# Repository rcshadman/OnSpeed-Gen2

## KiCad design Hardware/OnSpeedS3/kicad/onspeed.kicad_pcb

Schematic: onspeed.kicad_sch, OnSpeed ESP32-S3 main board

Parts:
C1: 22uF 100V; CP_Elec_8x10; Rating 100V, damps the input filter; above the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; MPN CS2A220M-CRF10; LCSC C116424
C2, C5: 100nF; C_0805_2012Metric; Rating 100V X7R; LCSC C28233
C3, C4: 2.2uF; C_1210_3225Metric; Rating 100V X7S; LCSC C86054
C6, C8, C47, C48: 2.2nF; C_0603_1608Metric; Rating 50V X7R; LCSC C1604
C7: 220pF; C_0805_2012Metric; Rating 50V C0G; LCSC C1805
C9, C10, C15, C20: 22uF; C_0805_2012Metric; Rating 25V X5R; LCSC C45783
C11, C12, C16, C18, C21, C22, C25, C26, C28, C29, C30, C31, C32, C33, C34, C36, C37, C40, C42, C43, C45, C49, C50, C51, C52, C53, C55, C57, C59: 100nF; C_0603_1608Metric; Rating 50V X7R; LCSC C14663
C13, C56: 4.7uF; C_0805_2012Metric; Rating 25V X5R; LCSC C1779
C14, C17, C19, C27, C41, C44, C46, C58: 10uF; C_0805_2012Metric; Rating 25V X5R; LCSC C15850
C23, C35: 1uF; C_0603_1608Metric; Rating 16V X7R; LCSC C15849
C24: 10nF; C_0603_1608Metric; Rating 50V X7R; LCSC C57112
C38, C39: 2.2uF; C_0603_1608Metric; Rating 16V X5R; LCSC C23630
C54: 4.7nF; C_0603_1608Metric; Rating 50V X7R; LCSC C53987
D1: SS210; D_SMA; MPN SS210; LCSC C14996
D2: SMBJ58A; D_SMB; MPN SMBJ58A; LCSC C10226
D3, D19: SS14; D_SMA; MPN SS14; LCSC C2480
D4: Green; LED_0603_1608Metric; MPN 19-217/GHC-YR1S2/3T; LCSC C72043
D5: Blue; LED_0603_1608Metric; MPN 19-217/BHC-ZL1M2RY/3T; LCSC C72041
D6, D7, D8, D10, D11, D12, D13, D14: 15V bidir ESD; D_SOD-323; MPN PESD15VL1BA; LCSC C2985482
D9: 24V bidir ESD; D_SOD-323; MPN PESD24VL1BA; LCSC C314263
D15, D16, D17, D18: BAT54S; SOT-23; MPN BAT54SLT1G; LCSC C19726
D20: PESD2CAN; SOT-23; MPN PESD2CAN; LCSC C2687131
F1: 0.75A 60V PTC; Fuse_2920_7451Metric; MPN MF-SM075/60-2; LCSC C210842
F2: 0.1A 15V PTC; Fuse_0603_1608Metric; MPN BSMD0603-010-15V; LCSC C883088
FB1: 220R@100MHz 2A; L_0805_2012Metric; MPN BLM21PG221SN1D; LCSC C85840
FB2, FB3, FB4: 600R@100MHz 1.3A; L_0603_1608Metric; MPN BLM18KG601SN1D; LCSC C85833
FID1, FID2, FID3: Fiducial; Fiducial_1mm_Mask2mm
H1, H2, H3, H4: M3; MountingHole_3.2mm_M3_Pad_Via
J1: USB-C 16P; USB_C_Receptacle_HRO_TYPE-C-31-M-12; MPN TYPE-C-31-M-12; LCSC C165948
J2: DA-15 female; DSUB-15_Female_Horizontal_P2.77x2.84mm_EdgePinOffset9.40mm_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; MPN DS1037-15FNAKT74-0CC; LCSC C77835
J3: JST-GH 4P; JST_GH_SM04B-GHS-TB_1x04-1MP_P1.25mm_Horizontal; MPN SM04B-GHS-TB(LF)(SN); LCSC C189895
J4: DE-9 male; DSUB-9_Male_Horizontal_P2.77x2.84mm_EdgePinOffset9.40mm_Hol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; MPN DS1037-09MNAKT74-0CC; LCSC C75750
J5: microSD push-pull; microSD_HC_Molex_104031-0811; MPN 104031-0811; LCSC C585350
JP1: CAN term; SolderJumper-2_P1.3mm_Open_RoundedPad1.0x1.5mm
L1: 33uH 1.8A shielded; L_Changjiang_FNR6045S; MPN FNR6045S330MT; LCSC C168083
R1: 330k; R_0603_1608Metric; LCSC C23137
R2, R4, R6, R9: 100k; R_0603_1608Metric; LCSC C25803
R3, R5: 31.6k; R_0603_1608Metric; LCSC C25967
R7: 150k; R_0603_1608Metric; LCSC C22807
R8: 8.2k; R_0603_1608Metric; LCSC C25981
R10, R11: 5.1k; R_0603_1608Metric; LCSC C23186
R12, R15, R38, R40, R42, R44: 470; R_0603_1608Metric; LCSC C23179
R13, R14, R37, R50, R52, R53, R54, R55, R56, R57: 10k; R_0603_1608Metric; LCSC C25804
R16, R25: 1k; R_0603_1608Metric; LCSC C21190
R17: 20k; R_0603_1608Metric; LCSC C4184
R18, R24: 150; R_0603_1608Metric; LCSC C22808
R19, R21, R22: 22k; R_0603_1608Metric; LCSC C31850
R20, R23: 5.6k; R_0603_1608Metric; LCSC C23189
R26: 0; R_0603_1608Metric; LCSC C21189
R27, R32: 200k; R_0603_1608Metric; LCSC C25811
R28, R29, R30, R31, R33, R34, R35, R36: 4.7k; R_0603_1608Metric; LCSC C23162
R39, R43: 560; R_0603_1608Metric; LCSC C23204
R41, R45: 100; R_0603_1608Metric; LCSC C22775
R46, R47, R48, R49: 120; R_0603_1608Metric; LCSC C22787
R51: 33; R_0603_1608Metric; LCSC C23140
SW1, SW2: Tactile 4.2x3.2mm; SW_SPST_PTS810; MPN PTS810SJG250SMTRLFS; LCSC C221895
TP1: VIN; TestPoint_Pad_D1.5mm
TP2: +5V; TestPoint_Pad_D1.5mm
TP3: +3V3; TestPoint_Pad_D1.5mm
TP4, TP5: GND; TestPoint_Pad_D1.5mm
TP6: EN; TestPoint_Pad_D1.5mm
TP7: BOOT; TestPoint_Pad_D1.5mm
TP8: U0TXD; TestPoint_Pad_D1.5mm
TP9: U0RXD; TestPoint_Pad_D1.5mm
U1: LM5164DDAR; SOIC-8-1EP_3.9x4.9mm_P1.27mm_EP2.95x4.9mm_Mask2.71x3.4mm_Th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; MPN LM5164DDAR; LCSC C477928
U2: USBLC6-2SC6; SOT-23-6; MPN USBLC6-2SC6; LCSC C7519
U3: LDL1117S33R; SOT-223-3_TabPin2; MPN LDL1117S33R; LCSC C435835
U4: ESP32-S3-WROOM-1-N8; ESP32-S3-WROOM-1_BodyCourtyard; MPN ESP32-S3-WROOM-1-N8; LCSC C2913198
U5, U6: MS4525DO-DS5AI001DP; MS4525DO_DIP8_500mil; MPN MS4525DO-DS5AI001DP
U7: SSCSRNN1.6BA7A3; Honeywell_SSC_SIP4_RN; MPN SSCSRNN1.6BA7A3
U8, U9: PCA9306DCUR; VSSOP-8_2.3x2mm_P0.5mm; MPN PCA9306DCUR; LCSC C33196
U10: ISM330DHCX; LGA-14_3x2.5mm_P0.5mm_LayoutBorder3x4y; MPN ISM330DHCXTR; LCSC C2655101
U11: PCM5102APWR; TSSOP-20_4.4x6.5mm_P0.65mm; MPN PCM5102APWR; LCSC C107671
U12: SP3232EEN-L/TR; SOIC-16_3.9x9.9mm_P1.27mm; MPN SP3232EEN-L/TR; LCSC C9378
U13: TJA1051T/3/1J; SOIC-8_3.9x4.9mm_P1.27mm; MPN TJA1051T/3/1J; LCSC C38695

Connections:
3V3_OUT_F: D19.2 (A), F2.2
+3V3: C15.1, C16.1, C20.1, C21.1, C22.1, C45.1, C46.1, C53.1, C57.1, C58.1, C59.1, D15.2 (K), D16.2 (K), D17.2 (K), D18.2 (K), F2.1, FB2.1, FB3.1, J5.4 (VDD), R9.2, R12.1, R13.1, R14.1, R17.1, R22.1, R52.1, R53.1, R54.1, R55.1, R56.1, R57.1, TP3.1, U3.2 (VO), U4.2 (3V3), U11.20 (DVDD), U12.16 (VCC), U13.5 (VIO)
+3V3_A: C19.1, C41.1, C42.1, C43.1, C44.1, FB3.2, U11.1 (CPVDD), U11.8 (AVDD)
+3V3_S: C17.1, C18.1, C30.1, C31.1, C32.1, C33.1, C34.1, C35.1, FB2.2, J3.1, R28.1, R29.1, R33.1, R34.1, U7.2 (VSUPPLY), U8.2 (VREF1), U9.2 (VREF1), U10.5 (VDDIO), U10.8 (VDD), U10.12 (CS)
+5V: C6.2, C9.1, C10.1, C11.1, C14.1, C55.1, C56.1, D3.1 (K), FB4.1, L1.2, R4.1, TP2.1, U3.3 (VI), U13.3 (VCC)
+5V_S: C27.1, C28.1, C29.1, FB4.2, R27.1, R30.1, R31.1, R32.1, R35.1, R36.1, U5.2 (VDD), U6.2 (VDD)
AUDIO_GND: J2.15, R26.1
AUDL_F: C47.1, R38.2, R39.1
AUDL_P: R39.2, R40.1, R41.1
AUDR_F: C48.1, R42.2, R43.1
AUDR_P: R43.2, R44.1, R45.1
BOOM_RX: D18.3 (COM), R25.2, U4.7 (IO7)
BOOT: R14.2, SW2.1, TP7.1, U4.27 (IO0)
BUCK_BST: C8.1, U1.7 (BST)
BUCK_EN: R1.2, R2.1, U1.3 (EN/UVLO)
BUCK_FB: C7.2, R4.2, R5.1, U1.5 (FB)
BUCK_RA: C6.1, C7.1, R6.2
BUCK_RON: R3.1, U1.4 (RON)
BUCK_SW: C8.2, L1.1, R6.1, U1.8 (SW)
CANH: D20.1 (K), J4.7, JP1.1 (A), U13.7 (CANH)
CANL: D20.2 (K), J4.2, R48.2, R49.2, U13.6 (CANL)
CAN_MID: C54.1, R46.2, R47.2, R48.1, R49.1
CAN_RX: U4.4 (IO4), U13.4 (RXD)
CAN_S: R50.1, U4.30 (IO37), U13.8 (S)
CAN_TH: JP1.2 (B), R46.1, R47.1
CAN_TX: U4.24 (IO47), U13.1 (TXD)
DAC_CAPM: C38.2, U11.4 (CAPM)
DAC_CAPP: C38.1, U11.2 (CAPP)
DAC_L: R38.1, U11.6 (OUTL)
DAC_LDOO: C40.1, U11.18 (LDOO)
DAC_R: R42.1, U11.7 (OUTR)
DAC_VNEG: C39.1, U11.5 (VNEG)
DAC_XSMT: R37.1, U4.23 (IO21), U11.17 (XSMT)
DISP_TX: R24.1, U4.18 (IO10)
EFIS_RX: U4.8 (IO15), U12.12 (R1OUT)
EFIS_TX: U4.19 (IO11), U12.11 (T1IN)
EN: C23.1, R13.2, SW1.1, TP6.1, U4.3 (EN)
FLAP_ADC: C25.1, D16.3 (COM), R19.2, R20.1, U4.39 (IO1)
GND: C1.2, C2.2, C3.2, C4.2, C5.2, C9.2, C10.2, C11.2, C12.2, C13.2, C14.2, C15.2, C16.2, C17.2, C18.2, C19.2, C20.2, C21.2, C22.2, C23.2, C24.2, C25.2, C26.2, C27.2, C28.2, C29.2, C30.2, C31.2, C32.2, C33.2, C34.2, C35.2, C36.2, C37.2, C39.2, C40.2, C41.2, C42.2, C43.2, C44.2, C45.2, C46.2, C47.2, C48.2, C51.2, C52.2, C53.2, C54.2, C55.2, C56.2, C57.2, C58.2, C59.2, D2.2 (A), D4.1 (K), D5.1 (K), D6.2 (A2), D7.2 (A2), D8.2 (A2), D9.2 (A2), D10.2 (A2), D11.2 (A2), D12.2 (A2), D13.2 (A2), D14.2 (A2), D15.1 (A), D16.1 (A), D17.1 (A), D18.1 (A), D20.3 (A), H1.1, H2.1, H3.1, H4.1, J1.A1 (GND), J1.A12 (GND), J1.B1 (GND), J1.B12 (GND), J1.S1 (SHIELD), J2.0 (PAD), J2.14, J3.4, J4.0 (PAD), J4.3, J4.5, J4.8, J5.6 (VSS), J5.10 (DET_A), J5.11 (SHIELD), R2.2, R3.2, R5.2, R8.2, R10.2, R11.2, R20.2, R23.2, R26.2, R37.2, R40.2, R44.2, R50.2, SW1.2, SW2.2, TP4.1, TP5.1, U1.1 (GND), U1.9 (EP), U2.2 (GND), U3.1 (GND), U4.1 (GND), U4.40 (GND), U4.41 (GND), U5.1 (GND), U6.1 (GND), U7.1 (GND), U8.1 (GND), U9.1 (GND), U10.1 (SDO/SA0), U10.2 (SDX), U10.3 (SCX), U10.6 (GND), U10.7 (GND), U11.3 (CPGND), U11.9 (AGND), U11.10 (DEMP), U11.11 (FLT), U11.12 (SCK), U11.16 (FMT), U11.19 (DGND), U12.10 (T2IN), U12.15 (GND), U13.2 (GND)
GPS_RX: U4.9 (IO16), U12.9 (R2OUT)
I2CA5_SCL: R31.2, U5.4 (SCL), U8.6 (SCL2)
I2CA5_SDA: R30.2, U5.3 (SDA), U8.5 (SDA2)
I2CA_SCL: R29.2, U4.17 (IO9), U7.4 (SCL), U8.3 (SCL1)
I2CA_SDA: R28.2, U4.12 (IO8), U7.3 (SDA), U8.4 (SDA1)
I2CA_VREF2: C36.1, R27.2, U8.7 (VREF2), U8.8 (EN)
I2CB5_SCL: R36.2, U6.4 (SCL), U9.6 (SCL2)
I2CB5_SDA: R35.2, U6.3 (SDA), U9.5 (SDA2)
I2CB_SCL: J3.2, R34.2, U4.11 (IO18), U9.3 (SCL1), U10.13 (SCL)
I2CB_SDA: J3.3, R33.2, U4.10 (IO17), U9.4 (SDA1), U10.14 (SDA)
I2CB_VREF2: C37.1, R32.2, U9.7 (VREF2), U9.8 (EN)
I2S_BCK: U4.20 (IO12), U11.13 (BCK)
I2S_DIN: U4.22 (IO14), U11.14 (DIN)
I2S_LRCK: U4.21 (IO13), U11.15 (LRCK)
IMU_INT1: U4.28 (IO35), U10.4 (INT1)
LED_OUT: R18.1, U4.6 (IO6)
LED_PWR: D4.2 (A), R12.2
LED_STAT: D5.2 (A), R15.2
PGOOD: R9.1, U1.6 (PGOOD), U4.25 (IO48)
RS232_EFIS_IN: J2.2, U12.13 (R1IN)
RS232_EFIS_OUT: J2.12, U12.14 (T1OUT)
RS232_GPS_IN: J2.4, U12.8 (R2IN)
RS_C1N: C49.2, U12.3 (C1-)
RS_C1P: C49.1, U12.1 (C1+)
RS_C2N: C50.2, U12.5 (C2-)
RS_C2P: C50.1, U12.4 (C2+)
RS_VN: C52.1, U12.6 (VS-)
RS_VP: C51.1, U12.2 (VS+)
SD_CLK: R51.1, U4.32 (IO39)
SD_CLK_C: J5.5 (CLK), R51.2
SD_CMD: J5.3 (CMD), R52.2, U4.33 (IO40)
SD_D0: J5.7 (DAT0), R53.2, U4.34 (IO41)
SD_D1: J5.8 (DAT1), R54.2
SD_D2: J5.1 (DAT2), R55.2
SD_D3: J5.2 (DAT3/CD), R56.2, U4.35 (IO42)
SD_DET: J5.9 (DET_B), R57.2, U4.29 (IO36)
STAT_LED: R15.1, U4.31 (IO38)
SW_IN: C24.1, D15.3 (COM), R16.2, R17.2, U4.5 (IO5)
U0RXD: TP9.1, U4.36 (RXD0)
U0TXD: TP8.1, U4.37 (TXD0)
USB_CC1: J1.A5 (CC1), R10.1
USB_CC2: J1.B5 (CC2), R11.1
USB_DM: J1.A7 (D-), J1.B7 (D-), U2.1 (I/O1), U2.6 (I/O1), U4.13 (IO19)
USB_DP: J1.A6 (D+), J1.B6 (D+), U2.3 (I/O2), U2.4 (I/O2), U4.14 (IO20)
VBUS: C13.1, D3.2 (A), J1.A4 (VBUS), J1.A9 (VBUS), J1.B4 (VBUS), J1.B9 (VBUS), U2.5 (VBUS)
VIN: C1.1, C3.1, C4.1, C5.1, FB1.2, R1.1, R7.1, TP1.1, U1.2 (VIN)
VIN_F: D1.2 (A), F1.2
VIN_P: C2.1, D1.1 (K), D2.1 (K), FB1.1
VIN_RAW: F1.1, J2.1
VIN_SENSE: C12.1, R7.2, R8.1, U4.15 (IO3)
VOL_ADC: C26.1, D17.3 (COM), R21.2, R22.2, R23.1, U4.38 (IO2)
X_3V3: D13.1 (A1), D19.1 (K), J2.11 (P111)
X_AUD_L: D8.1 (A1), J2.6, R41.2
X_AUD_R: D10.1 (A1), J2.8, R45.2
X_BOOM: D14.1 (A1), J2.13, R25.1
X_DISP: D11.1 (A1), J2.9, R24.2
X_FLAP: D9.1 (A1), J2.7, R19.1
X_LED: D7.1 (A1), J2.5, R18.2
X_SW: D6.1 (A1), J2.3, R16.1
X_VOL: D12.1 (A1), J2.10, R21.1

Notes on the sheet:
1 Aircraft power in, protection, 5 V buck (LM5164)
2 USB-C (power + flashing), 3.3 V LDO, filtered rails
3 ESP32-S3-WROOM-1-N8
4 DB-15 harness (Gen2 pinout) and line protection
5 Pressure sensors (Gen2 positions) and ISM330DHCX IMU
6 Audio: PCM5102A and 600 ohm intercom pad
7 RS-232 (EFIS in/out, GPS in): SP3232E
8 CAN-FiX (MakerPlane): TJA1051T/3, DE-9 male
9 microSD logging (1-bit SDMMC)
10 Mechanical: grounded M3 holes, fiducials
Order of protection: PTC (over-current) -> SS210 (reverse polarity) -> SMBJ58A (clamps 93.6 V, under the LM5164 100 V rating, so load dump and 28 V surges ride through) -> ferrite + 47 uF damped filter -> LM5164 (100 V rated).
USB VBUS feeds +5V through SS14, so the board runs and flashes from a laptop with no aircraft power. With both present the buck (5.0 V) carries the load.
Strapping: IO0 BOOT button + 10k up; IO3 carries the VIN monitor (strap only used if the JTAG eFuse is set); IO45/IO46 left open (internal pull-downs: 3.3 V flash, normal boot).
Every external line has a 15 V bidirectional ESD diode at the connector (flap may see 14 V; audio swings both ways). RS-232 lines rely on the SP3232E's own +/-15 kV protection.
Two MS4525DO share address 0x28, so each sits on its own bus (as the firmware expects).
Pad: 2.1 Vrms DAC -> about 0.39 Vrms into a 600 ohm panel input, source impedance about 420 ohm. DAC load stays above 1 kohm. PCM5102A outputs are ground-centred, so no DC blocking is needed.
Unused T2IN tied low so it cannot float.
DE-9: 2 CAN-L, 7 CAN-H, 3 CAN GND, 5 GND, 8 shield; pin 1 bus power not used.

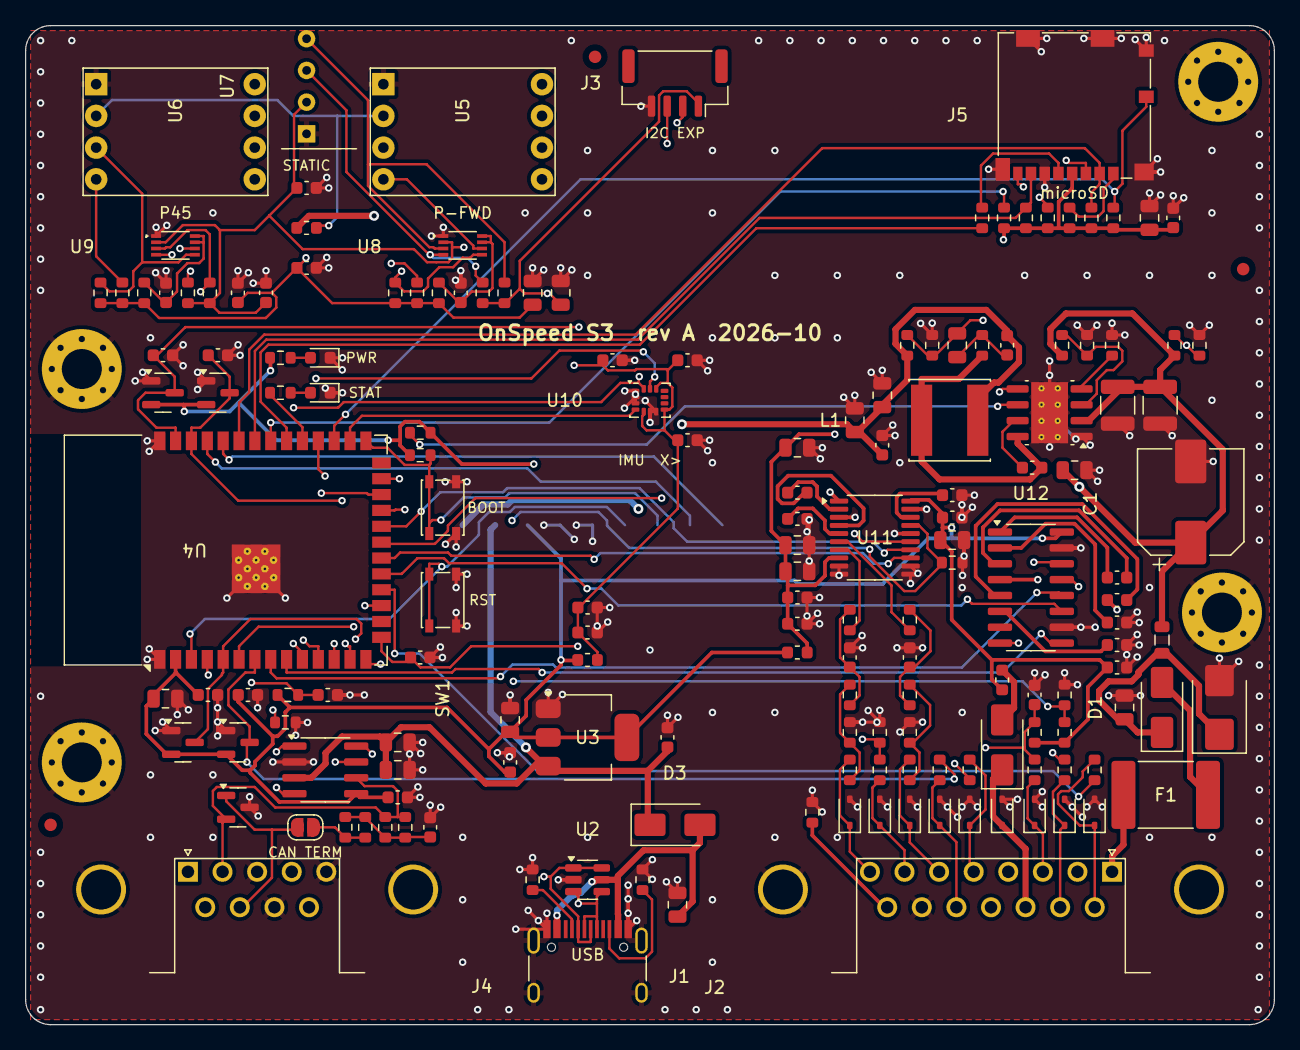
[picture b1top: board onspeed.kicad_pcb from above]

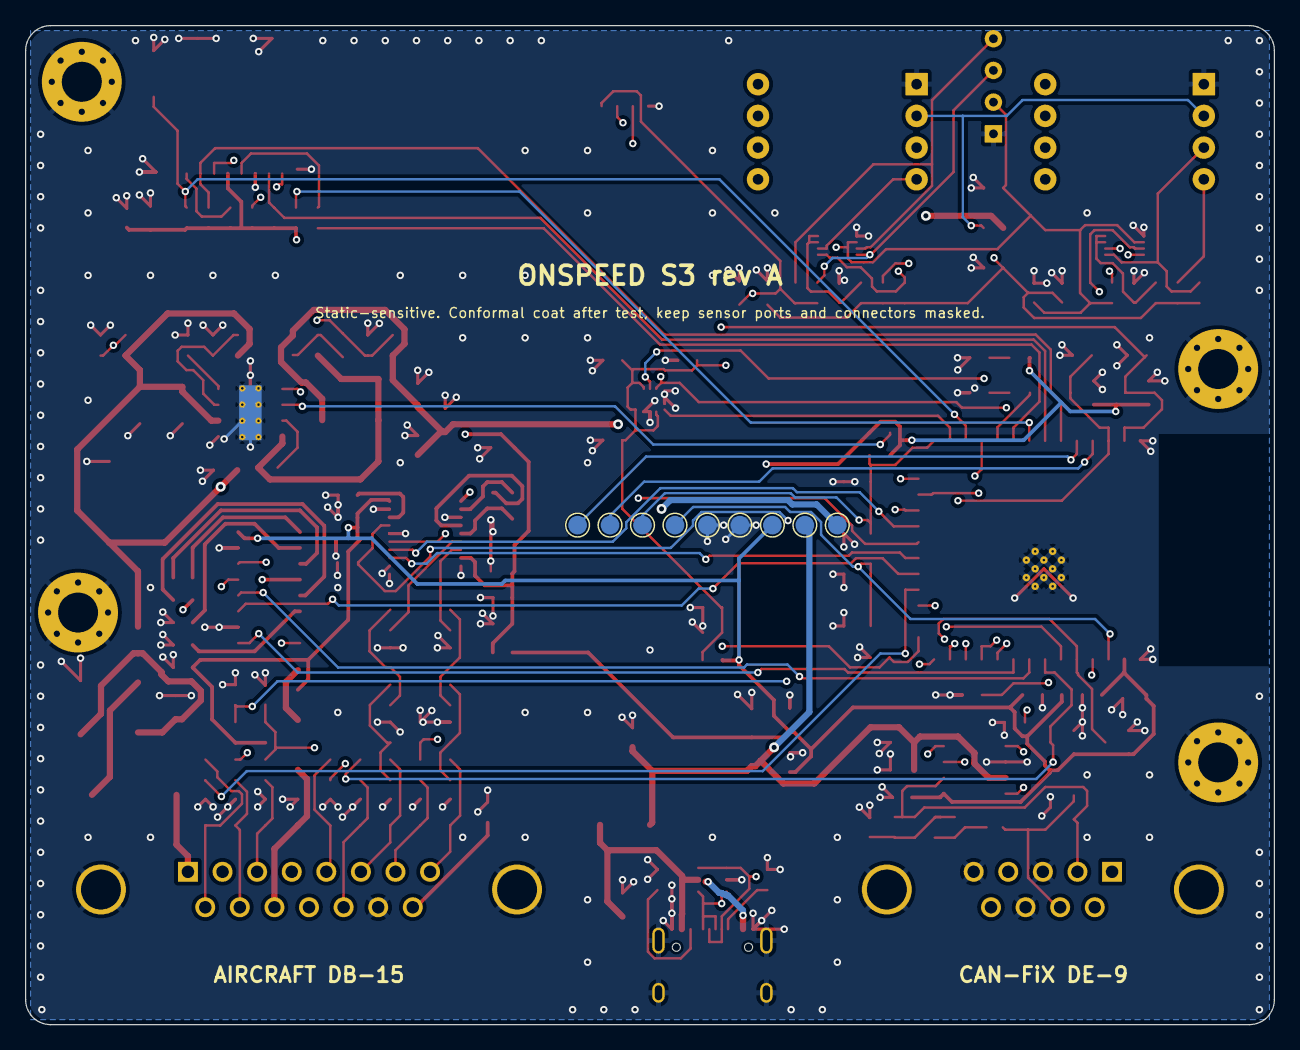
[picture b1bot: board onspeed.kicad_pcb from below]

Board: 4 copper layers, 100.0 x 80.0 mm, 180 parts (9 on the bottom side), 99 nets.

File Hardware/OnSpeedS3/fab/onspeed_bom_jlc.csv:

Comment,Designator,Footprint,LCSC Part #,MPN,Qty
22uF 100V,C1,CP_Elec_8x10,C116424,CS2A220M-CRF10,1
100nF,"C2,C5",C_0805_2012Metric,C28233,,2
2.2uF,"C3,C4",C_1210_3225Metric,C86054,,2
2.2nF,"C6,C8,C47,C48",C_0603_1608Metric,C1604,,4
220pF,C7,C_0805_2012Metric,C1805,,1
22uF,"C9,C10,C15,C20",C_0805_2012Metric,C45783,,4
100nF,"C11,C12,C16,C18,C21,C22,C25,C26,C28,C29,C30,C31,C32,C33,C34,C36,C37,C40,C42,C43,C45,C49,C50,C51,C52,C53,C55,C57,C59",C_0603_1608Metric,C14663,,29
4.7uF,"C13,C56",C_0805_2012Metric,C1779,,2
10uF,"C14,C17,C19,C27,C41,C44,C46,C58",C_0805_2012Metric,C15850,,8
1uF,"C23,C35",C_0603_1608Metric,C15849,,2
10nF,C24,C_0603_1608Metric,C57112,,1
2.2uF,"C38,C39",C_0603_1608Metric,C23630,,2
4.7nF,C54,C_0603_1608Metric,C53987,,1
SS210,D1,D_SMA,C14996,SS210,1
SMBJ58A,D2,D_SMB,C10226,SMBJ58A,1
SS14,"D3,D19",D_SMA,C2480,SS14,2
Green,D4,LED_0603_1608Metric,C72043,19-217/GHC-YR1S2/3T,1
Blue,D5,LED_0603_1608Metric,C72041,19-217/BHC-ZL1M2RY/3T,1
15V bidir ESD,"D6,D7,D8,D10,D11,D12,D13,D14",D_SOD-323,C2985482,PESD15VL1BA,8
24V bidir ESD,D9,D_SOD-323,C314263,PESD24VL1BA,1
BAT54S,"D15,D16,D17,D18",SOT-23,C19726,BAT54SLT1G,4
PESD2CAN,D20,SOT-23,C2687131,PESD2CAN,1
0.75A 60V PTC,F1,Fuse_2920_7451Metric,C210842,MF-SM075/60-2,1
0.1A 15V PTC,F2,Fuse_0603_1608Metric,C883088,BSMD0603-010-15V,1
220R@100MHz 2A,FB1,L_0805_2012Metric,C85840,BLM21PG221SN1D,1
600R@100MHz 1.3A,"FB2,FB3,FB4",L_0603_1608Metric,C85833,BLM18KG601SN1D,3
USB-C 16P,J1,USB_C_Receptacle_HRO_TYPE-C-31-M-12,C165948,TYPE-C-31-M-12,1
DA-15 female,J2,DSUB-15_Female_Horizontal_P2.77x2.84mm_EdgePinOffset9.40mm_Holes33.32mm,C77835,DS1037-15FNAKT74-0CC,1
JST-GH 4P,J3,JST_GH_SM04B-GHS-TB_1x04-1MP_P1.25mm_Horizontal,C189895,SM04B-GHS-TB(LF)(SN),1
DE-9 male,J4,DSUB-9_Male_Horizontal_P2.77x2.84mm_EdgePinOffset9.40mm_Holes24.99mm,C75750,DS1037-09MNAKT74-0CC,1
microSD push-pull,J5,microSD_HC_Molex_104031-0811,C585350,104031-0811,1
33uH 1.8A shielded,L1,L_Changjiang_FNR6045S,C168083,FNR6045S330MT,1
330k,R1,R_0603_1608Metric,C23137,,1
100k,"R2,R4,R6,R9",R_0603_1608Metric,C25803,,4
31.6k,"R3,R5",R_0603_1608Metric,C25967,,2
150k,R7,R_0603_1608Metric,C22807,,1
8.2k,R8,R_0603_1608Metric,C25981,,1
5.1k,"R10,R11",R_0603_1608Metric,C23186,,2
470,"R12,R15,R38,R40,R42,R44",R_0603_1608Metric,C23179,,6
10k,"R13,R14,R37,R50,R52,R53,R54,R55,R56,R57",R_0603_1608Metric,C25804,,10
1k,"R16,R25",R_0603_1608Metric,C21190,,2
20k,R17,R_0603_1608Metric,C4184,,1
150,"R18,R24",R_0603_1608Metric,C22808,,2
22k,"R19,R21,R22",R_0603_1608Metric,C31850,,3
5.6k,"R20,R23",R_0603_1608Metric,C23189,,2
0,R26,R_0603_1608Metric,C21189,,1
200k,"R27,R32",R_0603_1608Metric,C25811,,2
4.7k,"R28,R29,R30,R31,R33,R34,R35,R36",R_0603_1608Metric,C23162,,8
560,"R39,R43",R_0603_1608Metric,C23204,,2
100,"R41,R45",R_0603_1608Metric,C22775,,2
120,"R46,R47,R48,R49",R_0603_1608Metric,C22787,,4
33,R51,R_0603_1608Metric,C23140,,1
Tactile 4.2x3.2mm,"SW1,SW2",SW_SPST_PTS810,C221895,PTS810SJG250SMTRLFS,2
LM5164DDAR,U1,SOIC-8-1EP_3.9x4.9mm_P1.27mm_EP2.95x4.9mm_Mask2.71x3.4mm_ThermalVias,C477928,LM5164DDAR,1
USBLC6-2SC6,U2,SOT-23-6,C7519,USBLC6-2SC6,1
LDL1117S33R,U3,SOT-223-3_TabPin2,C435835,LDL1117S33R,1
ESP32-S3-WROOM-1-N8,U4,ESP32-S3-WROOM-1_BodyCourtyard,C2913198,ESP32-S3-WROOM-1-N8,1
MS4525DO-DS5AI001DP,"U5,U6",MS4525DO_DIP8_500mil,,MS4525DO-DS5AI001DP,2
SSCSRNN1.6BA7A3,U7,Honeywell_SSC_SIP4_RN,,SSCSRNN1.6BA7A3,1
PCA9306DCUR,"U8,U9",VSSOP-8_2.3x2mm_P0.5mm,C33196,PCA9306DCUR,2
ISM330DHCX,U10,LGA-14_3x2.5mm_P0.5mm_LayoutBorder3x4y,C2655101,ISM330DHCXTR,1
PCM5102APWR,U11,TSSOP-20_4.4x6.5mm_P0.65mm,C107671,PCM5102APWR,1
SP3232EEN-L/TR,U12,SOIC-16_3.9x9.9mm_P1.27mm,C9378,SP3232EEN-L/TR,1
TJA1051T/3/1J,U13,SOIC-8_3.9x4.9mm_P1.27mm,C38695,TJA1051T/3/1J,1

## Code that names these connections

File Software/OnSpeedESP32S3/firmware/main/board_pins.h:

// Pin map for the ESP32-S3-DevKitC-1 (ESP32-S3-WROOM-1 N8R8) prototype and the OnSpeed S3 custom board
// (Hardware/OnSpeedS3, WROOM-1 N8, no PSRAM). Every pin below is the same on both. Avoided: strapping pins 0/45/46 and USB 19/20
// (console runs on USB-Serial-JTAG), 43/44 (UART0, boot ROM output). GPIO3 is a strap only once the JTAG-select eFuse is burned, so the
// custom board uses it for the VIN monitor. On the DevKitC, 35-37 are octal PSRAM and 38/48 the RGB LED; the custom board (N8, no PSRAM)
// uses them in the ONSPEED_BOARD_S3 block below.
// Source: /mnt/project-files/onspeed-port/hardware-verification.md (pin audit).
#pragma once

// I2C bus A: Pfwd MS4525DO (0x28) + static SSCSRNN1.6BA7A3 (0x78). External 4.7k pull-ups required.
#define PIN_I2C_A_SDA 8
#define PIN_I2C_A_SCL 9
// I2C bus B: P45 MS4525DO (0x28) + ISM330DHCX IMU (0x6A). External 4.7k pull-ups required.
#define PIN_I2C_B_SDA 17
#define PIN_I2C_B_SCL 18
#define I2C_HZ 400000          // ESP32-S3 maximum (Gen2 Teensy ran these buses faster)

// Analog inputs on ADC1 (ADC2 is unusable while Wi-Fi runs)
#define ADC_CH_FLAP 0          // GPIO1, DB-15 pin 7, Gen2 divider 22k/5.6k + 100 nF
#define ADC_CH_VOLUME 1        // GPIO2, DB-15 pin 10

// PCM5102A I2S DAC
#define PIN_I2S_BCLK 12
#define PIN_I2S_WS 13
#define PIN_I2S_DOUT 14
#define PIN_DAC_XSMT 21        // 10k pull-down on the board keeps the DAC muted until firmware is up

// Serial
#define PIN_DISPLAY_TX 10      // M5Stack "#1" sentences, 115200 8N1, 3.3 V TTL
#define PIN_EFIS_TX 11         // MAX3232 T1IN
#define PIN_EFIS_RX 15         // MAX3232 R1OUT (Garmin G5 / G3X / Dynon / MGL)
#define PIN_GPS_RX 16          // MAX3232 R2OUT (VN-300)
#define PIN_BOOM_RX 7          // 3.3 V TTL only

// CAN-FiX (MakerPlane EFIS), 125 kbit/s. Custom board: TJA1051T/3 (VCC 5 V, VIO 3.3 V)
#define PIN_CAN_TX 47
#define PIN_CAN_RX 4

// Panel
#define PIN_PANEL_SWITCH 5
#define PIN_AOA_LED 6

// microSD, 1-bit SDMMC
#define PIN_SD_CLK 39
#define PIN_SD_CMD 40
#define PIN_SD_D0 41
#define PIN_SD_D3 42

// Custom board only (OnSpeed S3 rev A). Define ONSPEED_BOARD_S3 when building for it. On the DevKitC these
// GPIOs carry the octal PSRAM (35-37) and the RGB LED (38, 48), so they must stay unused there.
#ifdef ONSPEED_BOARD_S3
#define PIN_IMU_INT1 35        // ISM330DHCX INT1, push-pull, no pull-up
#define PIN_SD_DET 36          // card detect, 10k pull-up
#define PIN_CAN_SILENT 37      // TJA1051 S: high = listen-only, 10k pull-down = normal
#define PIN_STATUS_LED 38      // blue LED, active high
#define PIN_PGOOD 48           // LM5164 PGOOD, 100k pull-up; low = 5 V rail out of regulation
#define ADC_CH_VIN 2           // GPIO3 (ADC1 CH2), aircraft bus: VIN = Vadc x (100k + 8.2k) / 8.2k
#define VIN_DIVIDER (158.2f / 8.2f)
// The two MS4525DO run from 5 V behind PCA9306 translators; firmware sees them at 0x28 on buses A and B
// exactly as on the prototype.
#endif

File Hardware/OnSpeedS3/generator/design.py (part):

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
# ================================================================= 1. power input and 5 V buck
b = Block("1  Aircraft power in, protection, 5 V buck (LM5164)", 20, 20, 400, 150)
J1_NETS = {}  # filled by the connector block; pin 1 is VIN_RAW
part("ptc_in", "F", "Device", "Polyfuse", {"1": "VIN_RAW", "2": "VIN_F"}, b.at(30, 25), 90)
part("rev", "D", "Diode", "SS210", {"1": "VIN_P", "2": "VIN_F"}, b.at(80, 25), 180)
part("tvs_in", "D", "Device", "D_Zener", {"1": "VIN_P", "2": "GND"}, b.at(120, 40), 90)
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      "9": "SD_DET", "10": "GND", "11": "GND"}, b.at(40, 50))
b.start_grid(15)
b.x += 95
R("33", "SD_CLK", "SD_CLK_C", b, "edge-rate damping")
for net in ("SD_CMD", "SD_D0", "SD_D1", "SD_D2", "SD_D3", "SD_DET"):
    R("10k", "+3V3", net, b)
C("10u", "+3V3", "GND", b); C("100n", "+3V3", "GND", b)
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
